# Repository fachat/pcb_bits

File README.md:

# PCB libraries and bits

This repository contains various symbol and footprint bits, as well as partial schematics to be re-used in other designs.

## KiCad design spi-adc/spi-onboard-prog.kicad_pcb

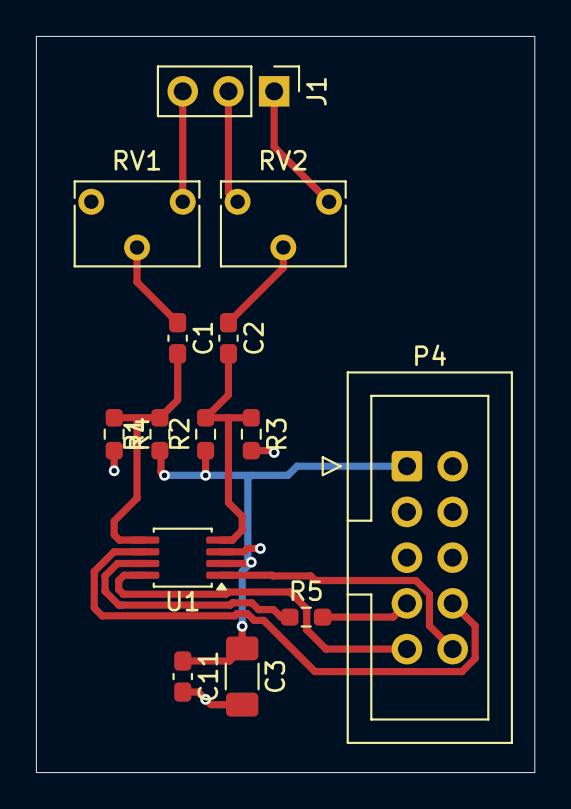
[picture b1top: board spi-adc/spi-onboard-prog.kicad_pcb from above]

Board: 2 copper layers, 27.7 x 40.9 mm, 14 parts (0 on the bottom side), 13 nets.

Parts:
C1, C2, C11: 100n; C_0603_1608Metric_Pad1.08x0.95mm_HandSolder
C3: 47u; C_1206_3216Metric_Pad1.33x1.80mm_HandSolder
J1: Conn_01x03; PinHeader_1x03_P2.54mm_Vertical
P4: IDC-Header_2x05_P2.54mm_Vertical
R1, R2, R3, R4: 4k7; R_0603_1608Metric_Pad0.98x0.95mm_HandSolder
R5: 100; R_0603_1608Metric_Pad0.98x0.95mm_HandSolder
RV1, RV2: 10k; Potentiometer_Bourns_3266W_Vertical
U1: ADC122S021; MSOP-8_3x3mm_P0.65mm

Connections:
3.3V: C3.1, C11.1, P4.1 (VCC), R1.1, R2.1, U1.2 (V_{A})
GND: C3.2, C11.2, J1.2, P4.2 (GND), R3.2, R4.2, RV1.3, RV2.3, U1.3 (GND)
MISO2: P4.7 (MISO), R5.2
MOSI: P4.8 (MOSI), U1.6 (DIN)
unnamed: C1.1, RV1.2
unnamed: C2.1, RV2.2
unnamed: J1.1, RV2.1
unnamed: J1.3, RV1.1
unnamed: R5.1, U1.7 (DOUT)
unnamed: C1.2, R1.2, R4.1, U1.5 (IN1)
unnamed: C2.2, R2.2, R3.1, U1.4 (IN2)
SCLK: P4.9 (CLK), U1.8 (SCLK)
/SS2: P4.10 (/SEL), U1.1 (~CS)

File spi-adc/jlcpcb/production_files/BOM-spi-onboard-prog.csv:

Comment,Designator,Footprint,LCSC,Quantity
100,R5,R_0603_1608Metric_Pad0.98x0.95mm_HandSolder,C22775,1
100n,"C1,C11,C2",C_0603_1608Metric_Pad1.08x0.95mm_HandSolder,C14663,3
10k,"RV1,RV2",Potentiometer_Bourns_3266W_Vertical,C123430,2
47u,C3,C_1206_3216Metric_Pad1.33x1.80mm_HandSolder,C96123,1
4k7,"R1,R2,R3,R4",R_0603_1608Metric_Pad0.98x0.95mm_HandSolder,C23162,4
ADC122S021,U1,MSOP-8_3x3mm_P0.65mm,C53084386,1
Conn_01x03,J1,PinHeader_1x03_P2.54mm_Vertical,C2937625,1

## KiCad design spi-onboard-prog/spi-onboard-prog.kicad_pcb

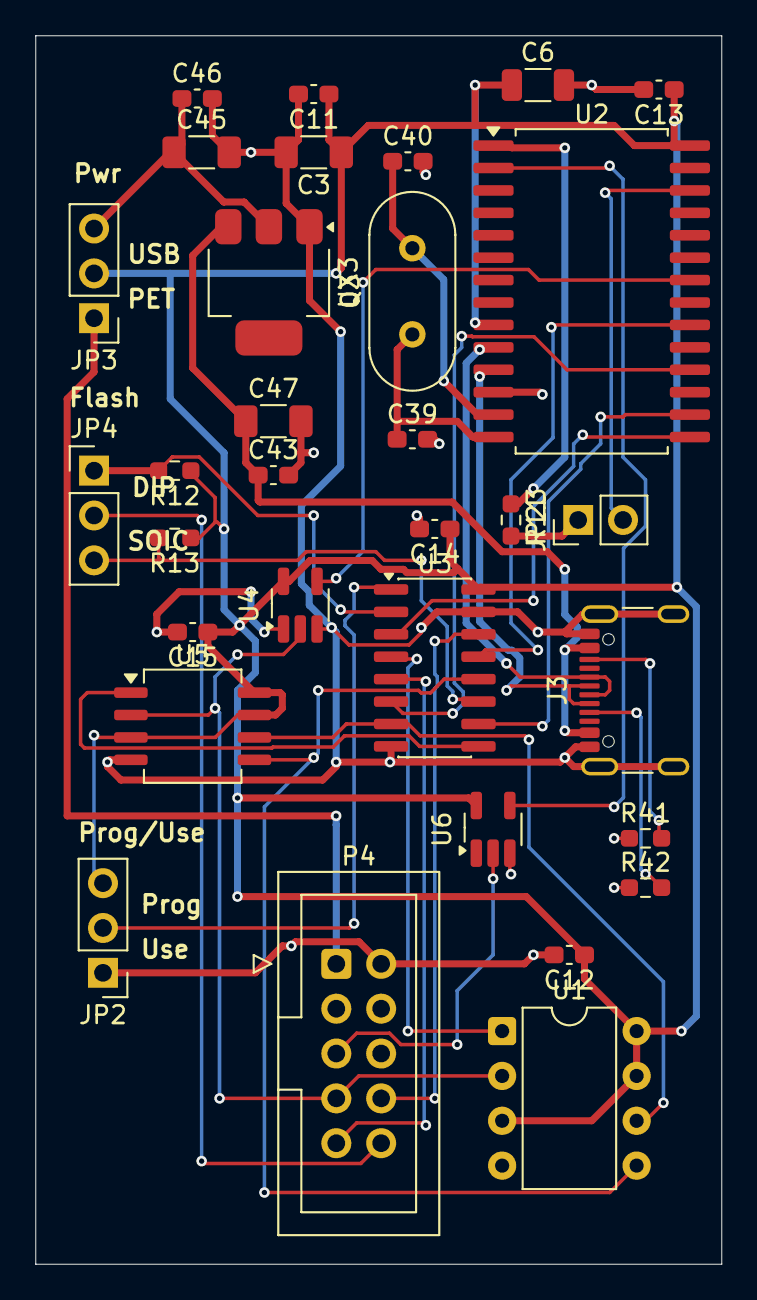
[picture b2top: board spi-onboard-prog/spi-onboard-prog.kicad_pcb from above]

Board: 2 copper layers, 38.9 x 69.6 mm, 32 parts (0 on the bottom side), 32 nets.

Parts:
C3, C45, C47: 47u; C_1206_3216Metric_Pad1.33x1.80mm_HandSolder
C6: 47u; C_1206_3216Metric
C11, C12, C13, C14, C15, C43, C46: 100n; C_0603_1608Metric_Pad1.08x0.95mm_HandSolder
C39, C40: 18p; C_0603_1608Metric_Pad1.08x0.95mm_HandSolder
J3: USB_C_Receptacle_USB2.0_16P; USB_C_Receptacle_GCT_USB4105-xx-A_16P_TopMnt_Horizontal
JP2, JP3, JP4: Jumper_3_Open; PinHeader_1x03_P2.54mm_Vertical
JP23: JP1E; PinHeader_1x02_P2.54mm_Vertical
P4: IDC-Header_2x05_P2.54mm_Vertical
Q3: 12MHz; Crystal_HC49-4H_Vertical
R11: 3k3; R_0603_1608Metric_Pad0.98x0.95mm_HandSolder
R12, R13: 47k; R_0603_1608Metric_Pad0.98x0.95mm_HandSolder
R41, R42: 5k1; R_0603_1608Metric_Pad0.98x0.95mm_HandSolder
U1: SST25VF080B-50-4x-S2Ax; DIP-8_W7.62mm
U2: CH341A; SOP-28_8.4x18.16mm_P1.27mm
U3: 74LVC257; SOIC-16_3.9x9.9mm_P1.27mm
U4: 74LVC1G125; SOT-23-5_HandSoldering
U5: SST25VF080B-50-4x-S2Ax; SOIC-8_5.3x6.2mm_P1.27mm
U6: 74LVC1G04; SOT-23-5_HandSoldering
UX3: LDI1117; SOT-223

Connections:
3.3V: C3.1, C6.1, C11.1, C12.1, C13.1, C14.1, C15.1, JP2.3 (B), JP3.2 (C), R12.1, R13.1, U1.3 (~WP), U1.7 (~HOLD), U1.8 (VDD), U2.9 (V3), U2.28 (VCC), U3.16 (VCC), U4.5 (VCC), U5.3 (~WP), U5.7 (~HOLD), U5.8 (VDD), U6.5 (VCC)
5V: C43.1, C47.1, J3.A4 (VBUS), J3.A9 (VBUS), J3.B4 (VBUS), J3.B9 (VBUS), UX3.3 (VI)
GND: C3.2, C6.2, C11.2, C12.2, C13.2, C14.2, C15.2, C39.2, C40.2, C43.2, C45.2, C46.2, C47.2, J3.A1 (GND), J3.A12 (GND), J3.B1 (GND), J3.B12 (GND), J3.SH (SHIELD), JP2.1 (A), P4.2 (GND), R41.1, R42.1, U1.4 (VSS), U2.12 (GND), U3.8 (GND), U3.15 (OE), U4.1, U4.3 (GND), U5.4 (VSS), U6.3 (GND), UX3.1 (GND)
MISO2: P4.7 (MISO), U1.2 (SO), U4.2, U5.2 (SO)
MOSI: P4.8 (MOSI), U3.14 (I0c)
unnamed: J3.A5 (CC1), R42.2
unnamed: J3.B5 (CC2), R41.2
unnamed: JP2.2 (C), U3.1 (S)
unnamed: JP3.1 (A), P4.1 (VCC)
unnamed: C45.1, C46.1, JP3.3 (B), UX3.2 (VO)
unnamed: JP4.1 (A), R12.2, U3.2 (I0a)
unnamed: JP4.3 (B), R13.2, U3.11 (I0d)
unnamed: JP23.1, R11.2
unnamed: U1.6 (SCK), U3.7 (Zb), U5.6 (SCK)
unnamed: U1.5 (SI), U3.12 (Zc), U5.5 (SI)
unnamed: U1.1 (~CE), U3.4 (Za)
unnamed: U2.2 (RSTI), U6.4
unnamed: JP23.2, U2.26 (TNOW/~INI/~RST)
unnamed: C40.1, Q3.2, U2.13 (XI)
unnamed: C39.1, Q3.1, U2.14 (XO)
unnamed: R11.1, U2.1 (~ACT)
unnamed: U3.9 (Zd), U5.1 (~CE)
SCLK: P4.9 (CLK), U3.5 (I0b)
UCD+: J3.A6 (D+), J3.B6 (D+), U2.10 (UD+)
UCD-: J3.A7 (D-), J3.B7 (D-), U2.11 (UD-)
USB_CS0: U2.15 (~CTS/D0), U3.3 (I1a)
USB_CS1: U2.16 (~DSR/D1), U3.10 (I1d)
USB_MISO: U2.22 (~SLP/D7), U4.4
USB_MOSI: U2.20 (~DTR/D5), U3.13 (I1c)
USB_SCK: U2.18 (~DCD/D3), U3.6 (I1b)
/RES: P4.5 (/RES), U6.2
/SS2: JP4.2 (C), P4.10 (/SEL)

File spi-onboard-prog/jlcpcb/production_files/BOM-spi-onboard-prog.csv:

Comment,Designator,Footprint,LCSC,Quantity
100n,"C11,C12,C13,C14,C15,C43,C46",C_0603_1608Metric_Pad1.08x0.95mm_HandSolder,C14663,7
12MHz,Q3,Crystal_HC49-4H_Vertical,C16369,1
18p,"C39,C40",C_0603_1608Metric_Pad1.08x0.95mm_HandSolder,C1647,2
3k3,R11,R_0603_1608Metric_Pad0.98x0.95mm_HandSolder,C22978,1
47k,"R12,R13",R_0603_1608Metric_Pad0.98x0.95mm_HandSolder,C25819,2
47u,"C3,C45,C47,C6",C_1206_3216Metric_Pad1.33x1.80mm_HandSolder,C96123,4
5k1,"R41,R42",R_0603_1608Metric_Pad0.98x0.95mm_HandSolder,C25197,2
74LVC1G04,U6,SOT-23-5_HandSoldering,C7827,1
74LVC1G125,U4,SOT-23-5_HandSoldering,C52140413,1
74LVC257,U3,SOIC-16_3.9x9.9mm_P1.27mm,C165622,1
CH341A,U2,SOP-28_8.4x18.16mm_P1.27mm,C13517,1
JP1E,JP23,PinHeader_1x02_P2.54mm_Vertical,C492401,1
Jumper_3_Open,"JP2,JP3,JP4",PinHeader_1x03_P2.54mm_Vertical,C49257,3
LDI1117,UX3,SOT-223,C6186,1
SST25VF080B-50-4x-S2Ax,U1,DIP-8_W7.62mm,C72124,1
SST25VF080B-50-4x-S2Ax,U5,SOIC-8_5.3x6.2mm_P1.27mm,C80925,1
USB_C_Receptacle_USB2.0_16P,J3,USB_C_Receptacle_GCT_USB4105-xx-A_16P_TopMnt_Horizontal,C2765186,1

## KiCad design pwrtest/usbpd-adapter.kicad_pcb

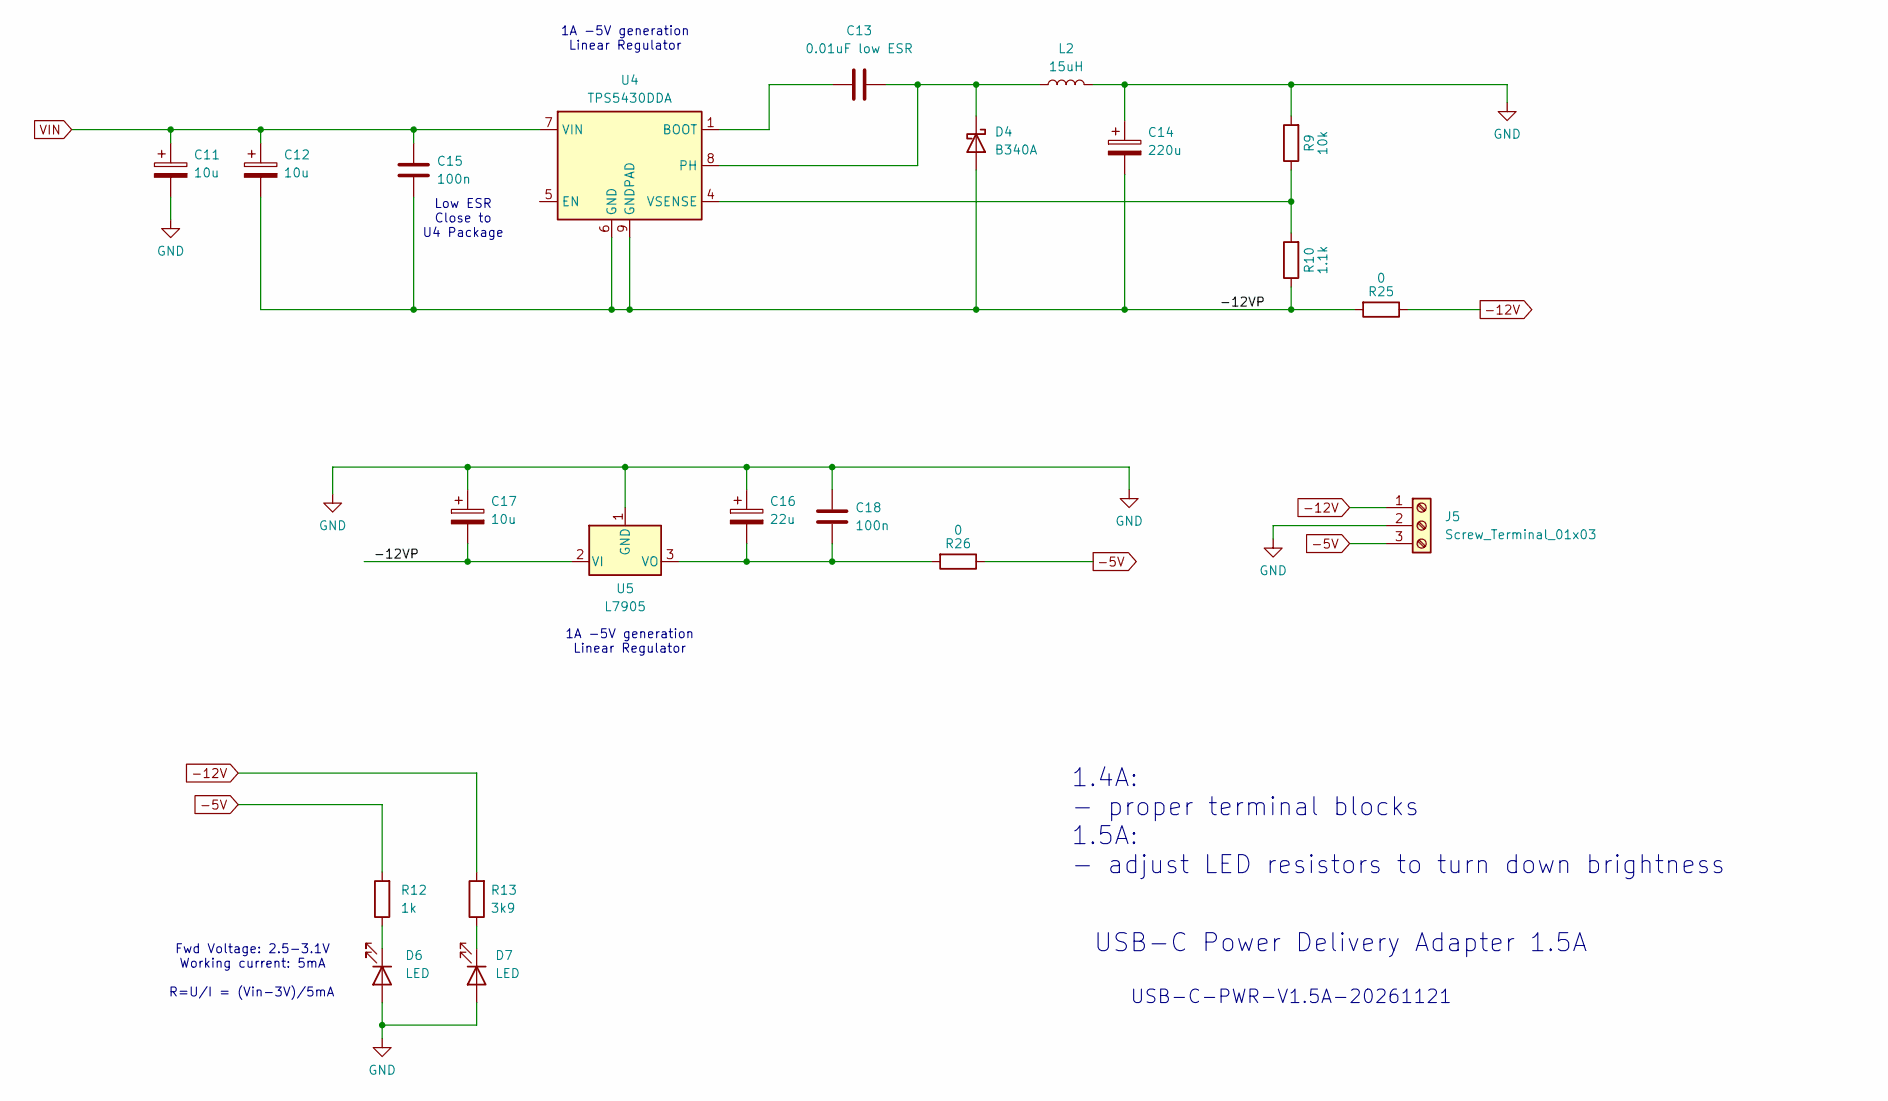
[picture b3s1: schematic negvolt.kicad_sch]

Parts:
C11, C12, C17: 10u; C_1206_3216Metric_Pad1.33x1.80mm_HandSolder; LCSC C13585
C13: 0.01uF low ESR; C_0603_1608Metric_Pad1.08x0.95mm_HandSolder; LCSC C57112
C14: 220u; CP_Elec_10x10; LCSC C125977
C15, C18: 100n; C_0603_1608Metric_Pad1.08x0.95mm_HandSolder; LCSC C14663
C16: 22u; C_1206_3216Metric_Pad1.33x1.80mm_HandSolder; LCSC C12891
D4: B340A; D_SMA_Handsoldering; LCSC C3018525
D6, D7: LED; D_0805_2012Metric_Pad1.15x1.40mm_HandSolder; LCSC C2297
J5: Screw_Terminal_01x03; TermBlock HB9500-3P; LCSC C60786
L2: 15uH; L_APV_APH0630; LCSC C5189959
R9: 10k; R_0603_1608Metric_Pad0.98x0.95mm_HandSolder; LCSC C25804
R10: 1.1k; R_0603_1608Metric_Pad0.98x0.95mm_HandSolder; LCSC C22764
R12: 1k; R_0603_1608Metric_Pad0.98x0.95mm_HandSolder; LCSC C21190
R13: 3k9; R_0603_1608Metric_Pad0.98x0.95mm_HandSolder; LCSC C23018
R25, R26: 0; R_0603_1608Metric_Pad0.98x0.95mm_HandSolder; LCSC C21189
U4: TPS5430DDA; TI_SO-PowerPAD-8_ThermalVias; LCSC C9864
U5: L7905; TO-252-3_TabPin2; LCSC C962758

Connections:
-5V: J5.3, R12.2, R26.1; also elsewhere on the board
-12V: J5.1, R13.2, R25.1; also elsewhere on the board
/Negative Voltages/-12VP: C12.2, C14.2, C15.2, C17.2, D4.2 (A), R10.1, R25.2, U4.6 (GND), U4.9 (GNDPAD), U5.2 (VI)
GND: C11.2, C14.1, C16.1, C17.1, C18.2, D6.2 (A), D7.2 (A), J5.2, L2.2, R9.2, U5.1 (GND); also elsewhere on the board
unnamed: C13.2, D4.1 (K), L2.1, U4.8 (PH)
unnamed: D6.1 (K), R12.1
unnamed: D7.1 (K), R13.1
unnamed: C13.1, U4.1 (BOOT)
unnamed: R9.1, R10.2, U4.4 (VSENSE)
unnamed: C16.2, C18.1, R26.2, U5.3 (VO)

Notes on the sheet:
USB-C-PWR-V1.5A-20261121
Fwd Voltage: 2.5-3.1V Working current: 5mA
R=U/I = (Vin-3V)/5mA
1A -5V generation Linear Regulator
USB-C Power Delivery Adapter 1.5A
Low ESR Close to U4 Package
1.4A: - proper terminal blocks 1.5A: - adjust LED resistors to turn down brightness

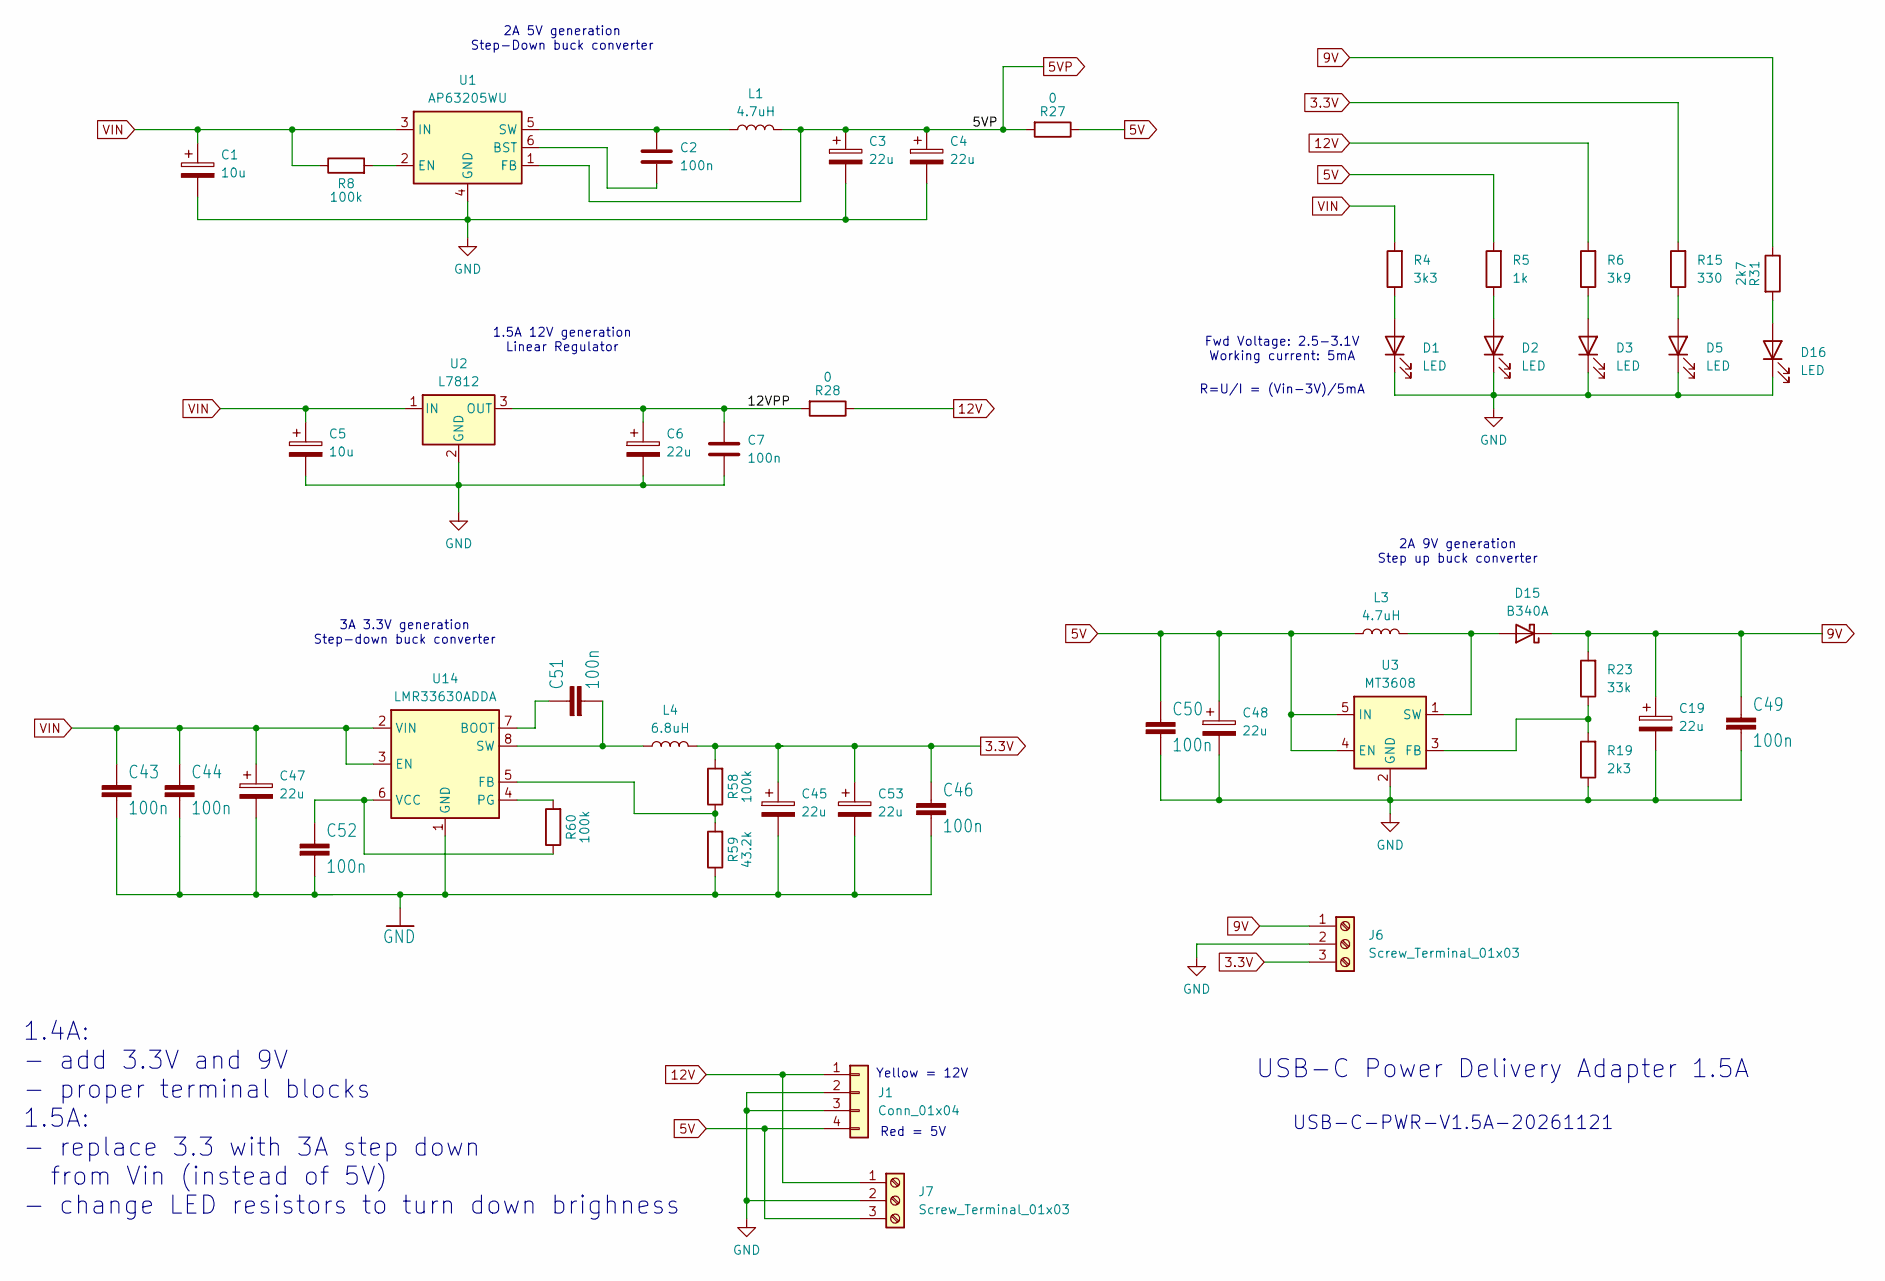
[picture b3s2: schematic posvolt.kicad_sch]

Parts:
C1, C5: 10u; C_1206_3216Metric_Pad1.33x1.80mm_HandSolder; LCSC C13585
C2, C7, C43, C44, C46, C49, C50, C51, C52: 100n; C_0603_1608Metric_Pad1.08x0.95mm_HandSolder; LCSC C14663
C3, C4, C6, C19, C45, C47, C48, C53: 22u; C_1206_3216Metric_Pad1.33x1.80mm_HandSolder; LCSC C12891
D1, D2, D3, D5, D16: LED; D_0805_2012Metric_Pad1.15x1.40mm_HandSolder; LCSC C2297
D15: B340A; D_SMA_Handsoldering; LCSC C3018525
J1: Conn_01x04; TE_MATE-N-LOK_350211-1_1x04_P5.08mm_Vertical
J6, J7: Screw_Terminal_01x03; TermBlock HB9500-3P; LCSC C60786
L1, L3: 4.7uH; L_APV_ANR4030; LCSC C57269
L4: 6.8uH; L_Sunlord_SWRB1205S; LCSC C2929498
R4: 3k3; R_0603_1608Metric_Pad0.98x0.95mm_HandSolder; LCSC C22978
R5: 1k; R_0603_1608Metric_Pad0.98x0.95mm_HandSolder; LCSC C21190
R6: 3k9; R_0603_1608Metric_Pad0.98x0.95mm_HandSolder; LCSC C23018
R8, R58, R60: 100k; R_0603_1608Metric_Pad0.98x0.95mm_HandSolder; LCSC C25803
R15: 330; R_0603_1608Metric_Pad0.98x0.95mm_HandSolder; LCSC C23138
R19: 2k3; R_0603_1608Metric_Pad0.98x0.95mm_HandSolder; LCSC C4190
R23: 33k; R_0603_1608Metric_Pad0.98x0.95mm_HandSolder; LCSC C4216
R27, R28: 0; R_0603_1608Metric_Pad0.98x0.95mm_HandSolder; LCSC C21189
R31: 2k7; R_0603_1608Metric_Pad0.98x0.95mm_HandSolder; LCSC C13167
R59: 43.2k; R_0603_1608Metric_Pad0.98x0.95mm_HandSolder; LCSC C23053
U1: AP63205WU; TSOT-23-6; LCSC C2071056
U2: L7812; TO-252-2; LCSC C26184
U3: MT3608; SOT-23-6; LCSC C84817
U14: LMR33630ADDA; Texas_HSOP-8-1EP_3.9x4.9mm_P1.27mm_ThermalVias; LCSC C841384

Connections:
3.3V: C45.1, C46.1, C53.1, J6.3, L4.2, R15.2, R58.2; also elsewhere on the board
5V: C48.1, C50.1, J1.4, J7.3, L3.1, R5.2, R27.1, U3.4 (EN), U3.5 (IN); also elsewhere on the board
5VP: C3.1, C4.1, L1.2, R27.2, U1.1 (FB); also elsewhere on the board
9V: C19.1, C49.1, D15.1 (K), J6.1, R23.2, R31.1; also elsewhere on the board
12V: J1.1, J7.1, R6.2, R28.1; also elsewhere on the board
/Positive Voltages/12VPP: C6.1, C7.2, R28.2, U2.3 (OUT)
GND: C1.2, C3.2, C4.2, C5.2, C6.2, C7.1, C19.2, C43.2, C44.2, C45.2, C46.2, C47.2, C48.2, C49.2, C50.2, C52.2, C53.2, D1.1 (K), D2.1 (K), D3.1 (K), D5.1 (K), D16.1 (K), J1.2, J1.3, J6.2, J7.2, R19.1, R59.1, U1.4 (GND), U2.2 (GND), U3.2 (GND), U14.1 (GND), U14.9 (GND); also elsewhere on the board
unnamed: D1.2 (A), R4.1
unnamed: D2.2 (A), R5.1
unnamed: D3.2 (A), R6.1
unnamed: D5.2 (A), R15.1
unnamed: D15.2 (A), L3.2, U3.1 (SW)
unnamed: D16.2 (A), R31.2
unnamed: C2.1, U1.6 (BST)
unnamed: R8.2, U1.2 (EN)
unnamed: C2.2, L1.1, U1.5 (SW)
unnamed: R19.2, R23.1, U3.3 (FB)
unnamed: C51.1, U14.7 (BOOT)
unnamed: R58.1, R59.2, U14.5 (FB)
unnamed: R60.2, U14.4 (PG)
unnamed: C51.2, L4.1, U14.8 (SW)
unnamed: C52.1, R60.1, U14.6 (VCC)

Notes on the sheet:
Red = 5V
1.4A: - add 3.3V and 9V - proper terminal blocks 1.5A: - replace 3.3 with 3A step down from Vin (instead of 5V) - change LED resistors to turn down brighness
Yellow = 12V
Fwd Voltage: 2.5-3.1V Working current: 5mA
2A 9V generation Step up buck converter
USB-C Power Delivery Adapter 1.5A
3A 3.3V generation Step-down buck converter
2A 5V generation Step-Down buck converter
1.5A 12V generation Linear Regulator
R=U/I = (Vin-3V)/5mA
USB-C-PWR-V1.5A-20261121

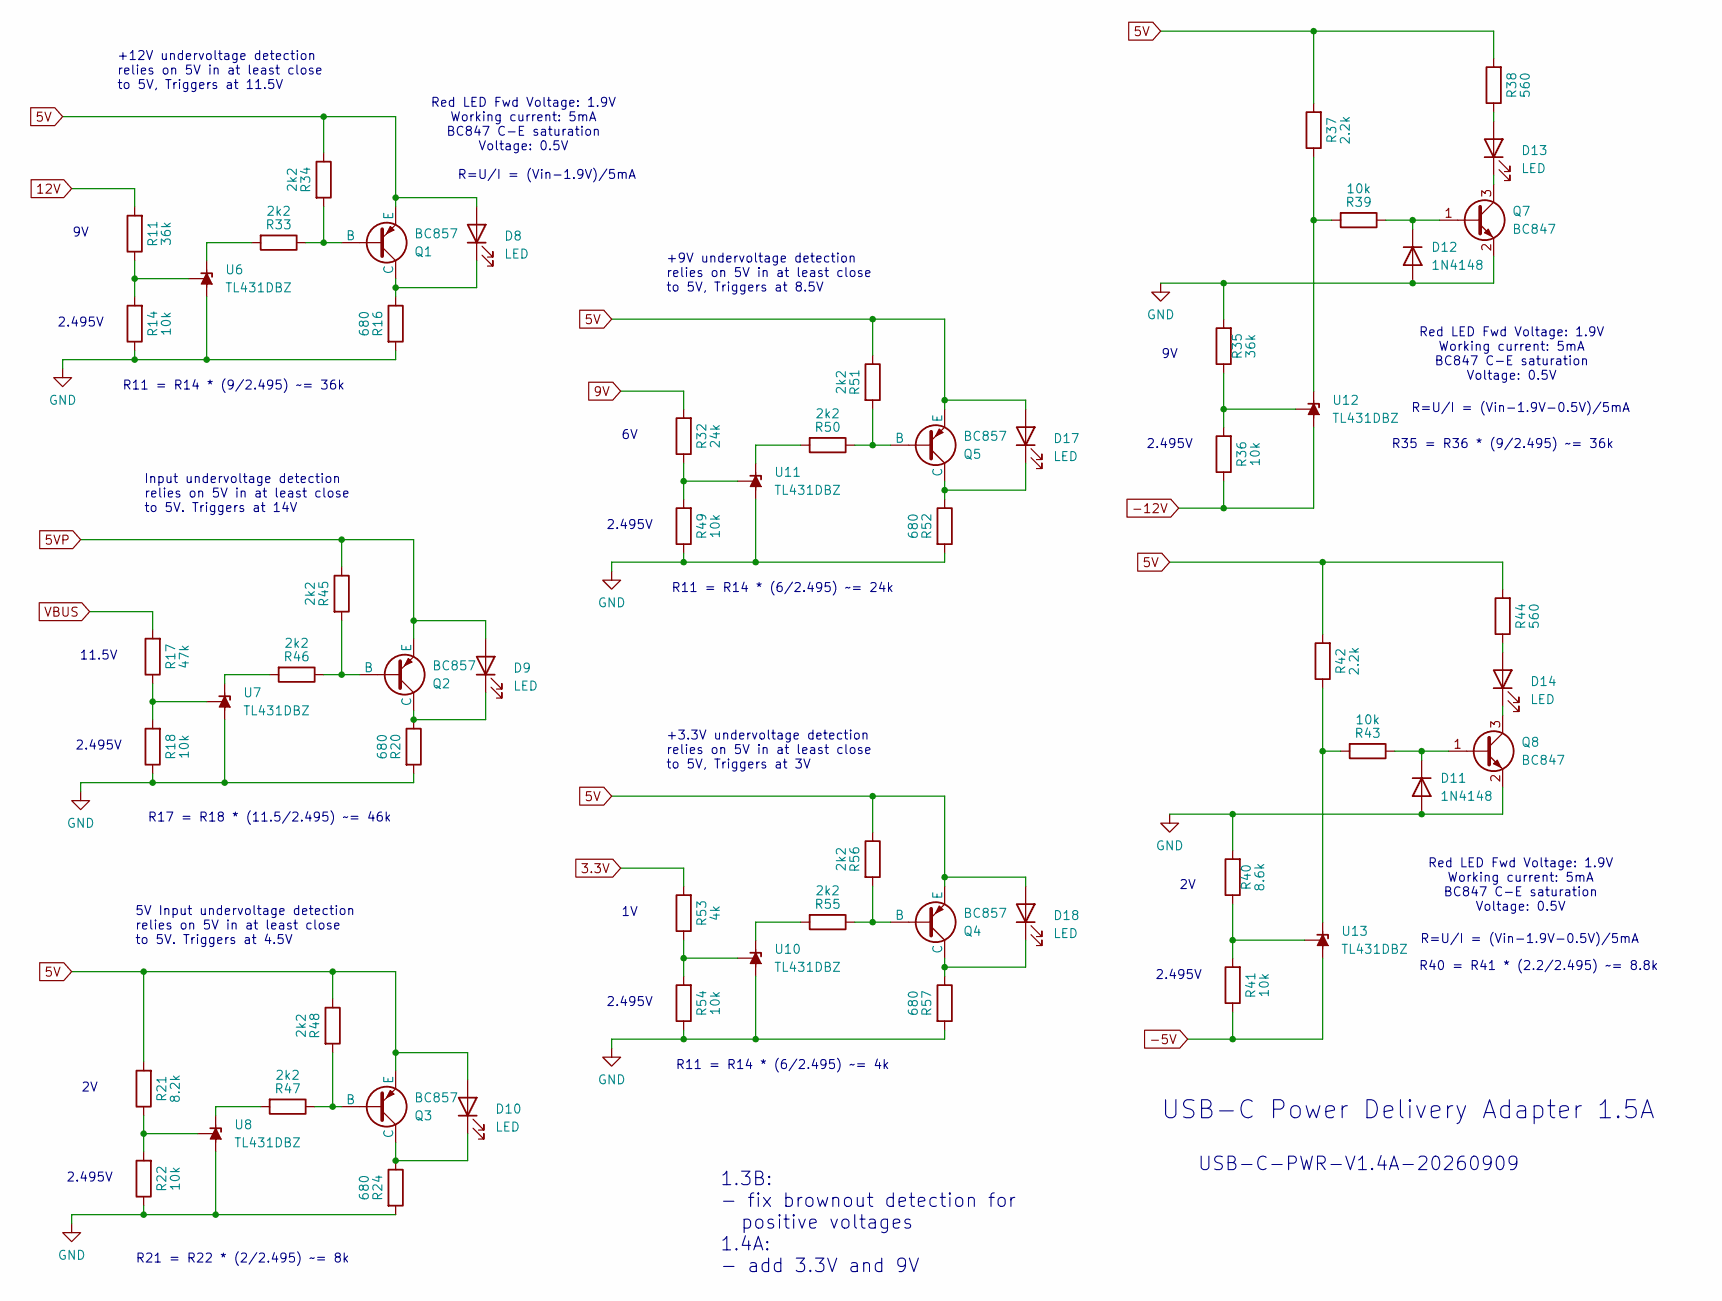
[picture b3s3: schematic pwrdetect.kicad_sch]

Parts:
D8, D9, D10, D13, D14, D17, D18: LED; D_0805_2012Metric_Pad1.15x1.40mm_HandSolder; LCSC C84256
D11, D12: 1N4148; D_SOD-323_HandSoldering; LCSC C2128
Q1, Q2, Q3, Q4, Q5: BC857; SOT-23; LCSC C20069137
Q7, Q8: BC847; SOT-23; LCSC C7420337
R11, R35: 36k; R_0603_1608Metric_Pad0.98x0.95mm_HandSolder; LCSC C23147
R14, R18, R22, R36, R39, R41, R43, R49, R54: 10k; R_0603_1608Metric_Pad0.98x0.95mm_HandSolder; LCSC C25804
R16, R20, R24, R52, R57: 680; R_0603_1608Metric_Pad0.98x0.95mm_HandSolder; LCSC C23228
R17: 47k; R_0603_1608Metric_Pad0.98x0.95mm_HandSolder; LCSC C25819
R21: 8.2k; R_0603_1608Metric_Pad0.98x0.95mm_HandSolder; LCSC C25981
R32: 24k; R_0603_1608Metric_Pad0.98x0.95mm_HandSolder; LCSC C23352
R33, R34, R45, R46, R47, R48, R50, R51, R55, R56: 2k2; R_0603_1608Metric_Pad0.98x0.95mm_HandSolder; LCSC C4190
R37, R42: 2.2k; R_0603_1608Metric_Pad0.98x0.95mm_HandSolder; LCSC C4190
R38, R44: 560; R_0603_1608Metric_Pad0.98x0.95mm_HandSolder; LCSC C23204
R40: 8.6k; R_0603_1608Metric_Pad0.98x0.95mm_HandSolder; LCSC C2924154
R53: 4k; R_0603_1608Metric_Pad0.98x0.95mm_HandSolder; LCSC C23018
U6, U7, U8: TL431DBZ; SOT-23; LCSC C19272793
U10, U11, U12, U13: TL431DBZ; SOT-23; LCSC C181103

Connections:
3.3V: R53.2; also elsewhere on the board
5V: D8.2 (A), D10.2 (A), D17.2 (A), D18.2 (A), Q1.2 (E), Q3.2 (E), Q4.2 (E), Q5.2 (E), R21.2, R34.1, R37.2, R38.2, R42.2, R44.2, R48.1, R51.1, R56.1; also elsewhere on the board
5VP: D9.2 (A), Q2.2 (E), R45.1; also elsewhere on the board
9V: R32.2; also elsewhere on the board
12V: R11.2; also elsewhere on the board
-5V: R41.1, U13.3 (A); also elsewhere on the board
-12V: R36.1, U12.3 (A); also elsewhere on the board
GND: D11.2 (A), D12.2 (A), Q7.2 (E), Q8.2 (E), R14.1, R16.2, R18.1, R20.2, R22.1, R24.2, R35.2, R40.2, R49.1, R52.2, R54.1, R57.2, U6.3 (A), U7.3 (A), U8.3 (A), U10.3 (A), U11.3 (A); also elsewhere on the board
unnamed: D8.1 (K), Q1.3 (C), R16.1
unnamed: D9.1 (K), Q2.3 (C), R20.1
unnamed: D10.1 (K), Q3.3 (C), R24.1
unnamed: D11.1 (K), Q8.1 (B), R43.1
unnamed: D12.1 (K), Q7.1 (B), R39.1
unnamed: D13.2 (A), R38.1
unnamed: D13.1 (K), Q7.3 (C)
unnamed: D14.2 (A), R44.1
unnamed: D14.1 (K), Q8.3 (C)
unnamed: D17.1 (K), Q5.3 (C), R52.1
unnamed: D18.1 (K), Q4.3 (C), R57.1
unnamed: Q1.1 (B), R33.1, R34.2
unnamed: Q2.1 (B), R45.2, R46.1
unnamed: Q3.1 (B), R47.1, R48.2
unnamed: Q4.1 (B), R55.1, R56.2
unnamed: Q5.1 (B), R50.1, R51.2
unnamed: R33.2, U6.2 (K)
unnamed: R11.1, R14.2, U6.1 (REF)
unnamed: R46.2, U7.2 (K)
unnamed: R17.1, R18.2, U7.1 (REF)
unnamed: R47.2, U8.2 (K)
unnamed: R21.1, R22.2, U8.1 (REF)
unnamed: R55.2, U10.2 (K)
unnamed: R53.1, R54.2, U10.1 (REF)
unnamed: R50.2, U11.2 (K)
unnamed: R32.1, R49.2, U11.1 (REF)
unnamed: R37.1, R39.2, U12.2 (K)
unnamed: R35.1, R36.2, U12.1 (REF)
unnamed: R42.1, R43.2, U13.2 (K)
unnamed: R40.1, R41.2, U13.1 (REF)

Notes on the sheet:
R21 = R22 * (2/2.495) ~= 8k
1.3B: - fix brownout detection for positive voltages 1.4A: - add 3.3V and 9V
R40 = R41 * (2.2/2.495) ~= 8.8k
R=U/I = (Vin-1.9V-0.5V)/5mA
2.495V
R=U/I = (Vin-1.9V)/5mA
11.5V
USB-C Power Delivery Adapter 1.5A
+3.3V undervoltage detection relies on 5V in at least close to 5V, Triggers at 3V
+9V undervoltage detection relies on 5V in at least close to 5V, Triggers at 8.5V
+12V undervoltage detection relies on 5V in at least close to 5V, Triggers at 11.5V
Red LED Fwd Voltage: 1.9V Working current: 5mA BC847 C-E saturation Voltage: 0.5V
R17 = R18 * (11.5/2.495) ~= 46k
R11 = R14 * (9/2.495) ~= 36k
USB-C-PWR-V1.4A-20260909
R11 = R14 * (6/2.495) ~= 24k
Input undervoltage detection relies on 5V in at least close to 5V. Triggers at 14V
5V Input undervoltage detection relies on 5V in at least close to 5V. Triggers at 4.5V
R11 = R14 * (6/2.495) ~= 4k
R35 = R36 * (9/2.495) ~= 36k

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
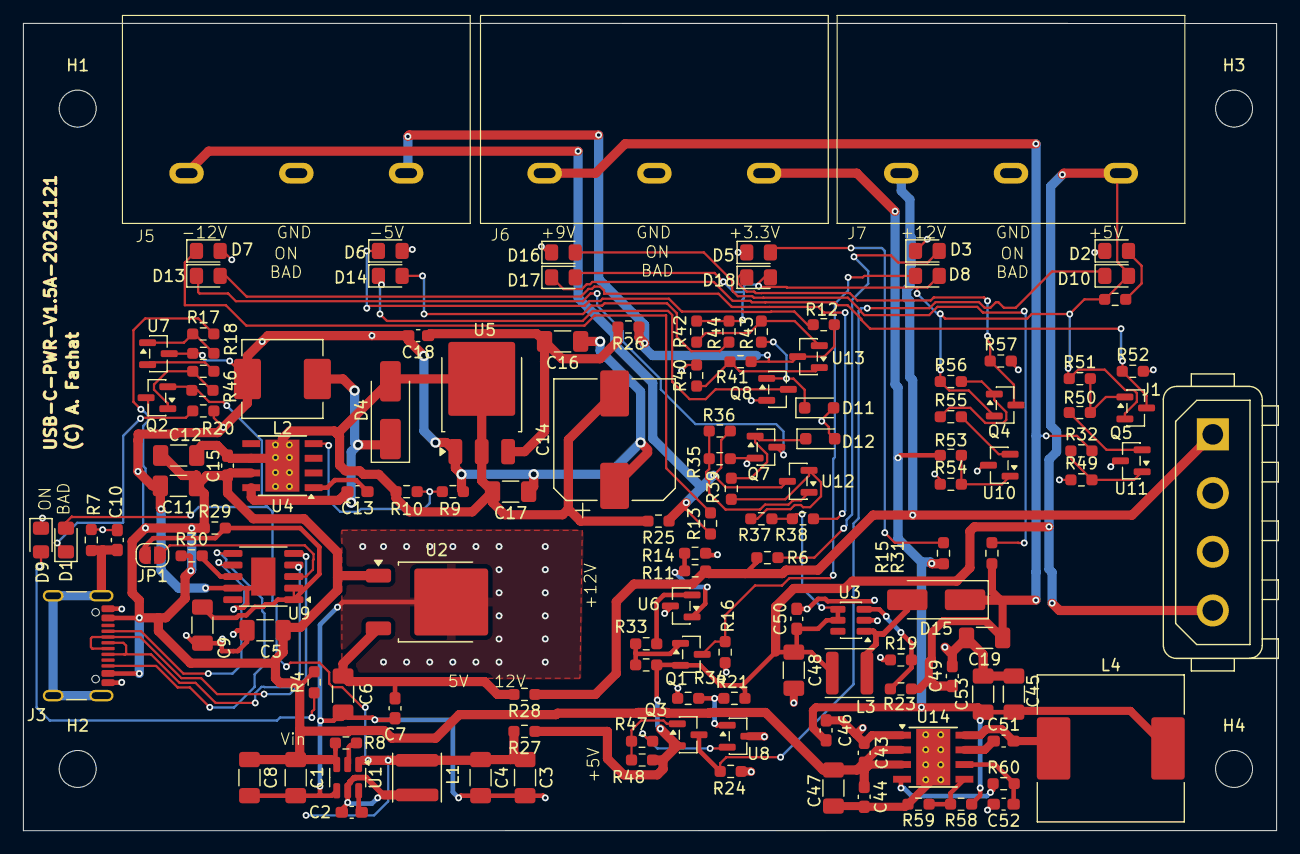
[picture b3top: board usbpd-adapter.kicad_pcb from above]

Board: 2 copper layers, 108.5 x 69.9 mm, 140 parts (0 on the bottom side), 70 nets.

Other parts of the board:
C8: 10u; C_1206_3216Metric_Pad1.33x1.80mm_HandSolder
C9: 1u; C_1206_3216Metric_Pad1.33x1.80mm_HandSolder
C10: 100n; C_0603_1608Metric_Pad1.08x0.95mm_HandSolder
H1, H2, H3, H4: MountingHole; MountingHole_3.2mm_M3_DIN965
J3: USB_C_Receptacle_USB2.0_16P; USB_C_Receptacle_GCT_USB4105-xx-A_16P_TopMnt_Horizontal
JP1: Jumper_2_Open; SolderJumper-2_P1.3mm_Open_RoundedPad1.0x1.5mm
R7: 5.1k; R_0603_1608Metric_Pad0.98x0.95mm_HandSolder
R29: 1k, >=0.3W; R_0603_1608Metric_Pad0.98x0.95mm_HandSolder
R30: 10k; R_0603_1608Metric_Pad0.98x0.95mm_HandSolder
U9: CH224K; SSOP-10-1EP_3.9x4.9mm_P1mm_EP2.1x3.3mm

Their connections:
GND: C8.2, C9.2, C10.2, J3.A1 (GND), J3.A12 (GND), J3.B1 (GND), J3.B12 (GND), R7.2, U9.9 (CFG1), U9.11 (GND); also elsewhere on the board
unnamed: J3.A5 (CC1), U9.7 (CC1)
unnamed: J3.B5 (CC2), U9.6 (CC2)
unnamed: C10.1, J3.S1 (SHIELD), R7.1
unnamed: JP1.1 (A), U9.3 (CFG3)
unnamed: C9.1, JP1.2 (B), R29.2, U9.1 (VDD), U9.2 (CFG2)
unnamed: J3.A7 (D-), J3.B7 (D-), U9.5 (DM)
unnamed: J3.A6 (D+), J3.B6 (D+), U9.4 (DP)
unnamed: R30.2, U9.8 (VBUS)

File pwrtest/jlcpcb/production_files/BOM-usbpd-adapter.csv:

Comment,Designator,Footprint,LCSC,Quantity
0,"R25,R26,R27,R28",R_0603_1608Metric_Pad0.98x0.95mm_HandSolder,C21189,4
0.01uF low ESR,C13,C_0603_1608Metric_Pad1.08x0.95mm_HandSolder,C57112,1
1.1k,R10,R_0603_1608Metric_Pad0.98x0.95mm_HandSolder,C22764,1
100k,"R58,R60,R8",R_0603_1608Metric_Pad0.98x0.95mm_HandSolder,C25803,3
100n,"C10,C15,C18,C2,C43,C44,C46,C49,C50,C51,C52,C7",C_0603_1608Metric_Pad1.08x0.95mm_HandSolder,C14663,12
10k,"R14,R18,R22,R30,R36,R39,R41,R43,R49,R54,R9",R_0603_1608Metric_Pad0.98x0.95mm_HandSolder,C25804,11
10u,"C1,C11,C12,C17,C5,C8",C_1206_3216Metric_Pad1.33x1.80mm_HandSolder,C13585,6
15uH,L2,L_APV_APH0630,C5189959,1
1N4148,"D11,D12",D_SOD-323_HandSoldering,C2128,2
1k,"R12,R5",R_0603_1608Metric_Pad0.98x0.95mm_HandSolder,C21190,2
"1k, >=0.3W",R29,R_0603_1608Metric_Pad0.98x0.95mm_HandSolder,C5886053,1
1u,C9,C_1206_3216Metric_Pad1.33x1.80mm_HandSolder,C1848,1
2.2k,"R37,R42",R_0603_1608Metric_Pad0.98x0.95mm_HandSolder,C4190,2
220u,C14,CP_Elec_10x10,C125977,1
22u,"C16,C19,C3,C4,C45,C47,C48,C53,C6",C_1206_3216Metric_Pad1.33x1.80mm_HandSolder,C12891,9
24k,R32,R_0603_1608Metric_Pad0.98x0.95mm_HandSolder,C23352,1
2k2,"R33,R34,R45,R46,R47,R48,R50,R51,R55,R56",R_0603_1608Metric_Pad0.98x0.95mm_HandSolder,C4190,10
2k3,R19,R_0603_1608Metric_Pad0.98x0.95mm_HandSolder,C4190,1
2k7,R31,R_0603_1608Metric_Pad0.98x0.95mm_HandSolder,C13167,1
330,R15,R_0603_1608Metric_Pad0.98x0.95mm_HandSolder,C23138,1
33k,R23,R_0603_1608Metric_Pad0.98x0.95mm_HandSolder,C4216,1
36k,"R11,R35",R_0603_1608Metric_Pad0.98x0.95mm_HandSolder,C23147,2
3k3,R4,R_0603_1608Metric_Pad0.98x0.95mm_HandSolder,C22978,1
3k9,"R13,R6",R_0603_1608Metric_Pad0.98x0.95mm_HandSolder,C23018,2
4.7uH,"L1,L3",L_APV_ANR4030,C57269,2
43.2k,R59,R_0603_1608Metric_Pad0.98x0.95mm_HandSolder,C23053,1
47k,R17,R_0603_1608Metric_Pad0.98x0.95mm_HandSolder,C25819,1
4k,R53,R_0603_1608Metric_Pad0.98x0.95mm_HandSolder,C23018,1
5.1k,R7,R_0603_1608Metric_Pad0.98x0.95mm_HandSolder,C23186,1
560,"R38,R44",R_0603_1608Metric_Pad0.98x0.95mm_HandSolder,C23204,2
6.8uH,L4,L_Sunlord_SWRB1205S,C2929498,1
680,"R16,R20,R24,R52,R57",R_0603_1608Metric_Pad0.98x0.95mm_HandSolder,C23228,5
8.2k,R21,R_0603_1608Metric_Pad0.98x0.95mm_HandSolder,C25981,1
8.6k,R40,R_0603_1608Metric_Pad0.98x0.95mm_HandSolder,C2924154,1
AP63205WU,U1,TSOT-23-6,C2071056,1
B340A,"D15,D4",D_SMA_Handsoldering,C3018525,2
BC847,"Q7,Q8",SOT-23,C7420337,2
BC857,"Q1,Q2,Q3,Q4,Q5",SOT-23,C20069137,5
CH224K,U9,SSOP-10-1EP_3.9x4.9mm_P1mm_EP2.1x3.3mm,C970725,1
L7812,U2,TO-252-2,C26184,1
L7905,U5,TO-252-3_TabPin2,C962758,1
LED,"D1,D16,D2,D3,D5,D6,D7",D_0805_2012Metric_Pad1.15x1.40mm_HandSolder,C2297,7
LED,"D10,D13,D14,D17,D18,D8,D9",D_0805_2012Metric_Pad1.15x1.40mm_HandSolder,C84256,7
LMR33630ADDA,U14,Texas_HSOP-8-1EP_3.9x4.9mm_P1.27mm_ThermalVias,C841384,1
MT3608,U3,SOT-23-6,C84817,1
Screw_Terminal_01x03,"J5,J6,J7",TermBlock HB9500-3P,C60786,3
TL431DBZ,"U10,U11,U12,U13",SOT-23,C181103,4
TL431DBZ,"U6,U7,U8",SOT-23,C19272793,3
TPS5430DDA,U4,TI_SO-PowerPAD-8_ThermalVias,C9864,1
USB_C_Receptacle_USB2.0_16P,J3,USB_C_Receptacle_GCT_USB4105-xx-A_16P_TopMnt_Horizontal,C2765186,1
Conn_01x04,J1,TE_MATE-N-LOK_350211-1_1x04_P5.08mm_Vertical,,1
